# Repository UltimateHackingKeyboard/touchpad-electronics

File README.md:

Ultimate Hacking Keyboard touchpad module
=========================================

Contained are the schematics and board layout KiCad files for the [Ultimate Hacking Keyboard](https://ultimatehackingkeyboard.com/) touchpad module.

Make sure to clone this repo with:

`git clone --recursive git@github.com:UltimateHackingKeyboard/touchpad-electronics.git`

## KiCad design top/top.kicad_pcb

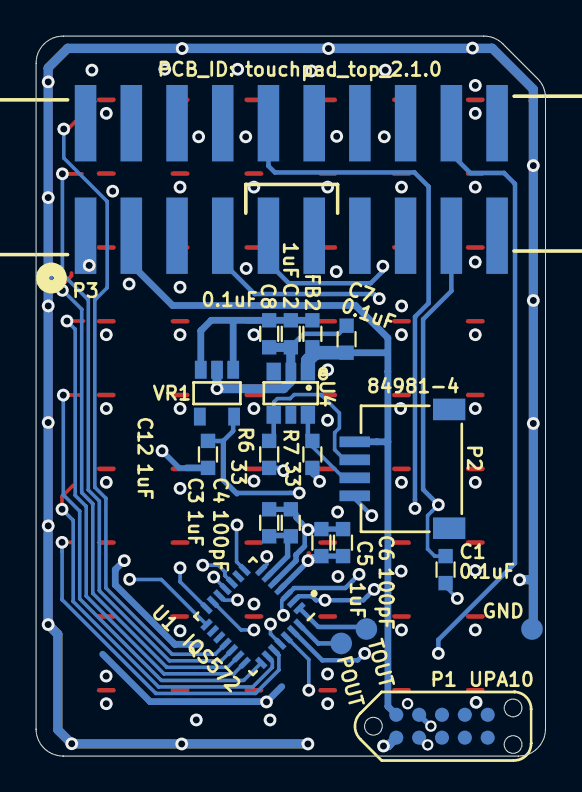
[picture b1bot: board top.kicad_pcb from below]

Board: 4 copper layers, 28.3 x 40.0 mm, 21 parts (21 on the bottom side), 14 nets.

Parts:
C1, C7, C8: 0.1uF; SM0603
C2, C3, C5, C12: 1uF; SM0603
C4, C6: 100pF; SM0603
FB2: FERRITE_BEAD; SM0603
P1: CONN_10; Tag_Connect_2x5_Header_With_No_Legs_Parallel_Numbering
P2: CONN_5; 84981-4
P3: CONN_20; MC-254-20-00-ST-SMD
R6, R7: 33; SM0603
TP_GND1: GND; Test_Point
TP_POUT1: POUT; Test_Point
TP_TOUT1: TOUT; Test_Point
U1: IQS572; QFN-28_4.3x4.3_Pitch0.5mm
U4: ESD; SC-74-TVS
VR1: MIC5504-3.3YM5; SOT-23-5

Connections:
+3V3: C5.2, C6.2, C12.2, U1.4, VR1.5
+5V: C2.2, C8.2, FB2.2, VR1.1, VR1.3
/NRST: C1.2, P3.17, U1.7
/PGM: P3.18, U1.27
/RDY: P3.10, U1.8
/SCL: P1.3, P3.9, R6.1, U1.3
/SCL_BOTTOM: P2.3, R6.2, U4.4
/SDA: P1.4, P3.7, R7.1, U1.2
/SDA_BOTTOM: P2.2, R7.2, U4.5
/VCC_BOTTOM: C7.2, FB2.1, P1.2, P2.4, P3.3, U4.1
GND: C1.1, C2.1, C3.1, C4.1, C5.1, C6.1, C7.1, C8.1, C12.1, P1.1, P2.1, P3.1, TP_GND1.1, U1.5, U4.2, VR1.2
unnamed: C3.2, C4.2, U1.6
unnamed: TP_POUT1.1, U1.28
unnamed: TP_TOUT1.1, U1.1

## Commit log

2019-07-03 Add root project file.
2019-07-03 Add gitignore.
2019-07-03 Add UGL KiCad lib as a git submodule.
2019-07-06 Add top board.
2019-07-06 Add bottom touchpad board.
2019-07-06 Put keepout areas to their actual layer.
2019-07-06 Add pogo pin connector.
2019-07-06 Add FFC connector on the bottom board.
2019-07-06 Add bottom schematic and route bottom board.
2019-07-06 Improve silk screen.
2019-07-06 Add top FFC connector.
2019-07-07 Replace circles with holes.
2019-07-07 Update description.
2019-07-11 Update library references.
2019-07-11 Add missing keepout areas.
2019-07-11 Add keepout areas.
2019-07-12 Update library reference.
2019-07-12 Add schematic and library links.
2019-07-12 Touch pattern #1.
2019-07-12 Touch pattern #2.
2019-07-12 Increase track width on bottom PCB.
2019-07-12 Annotate schematic.
2019-07-12 Add via pattern.
2019-07-12 Change touchpad sensor footprint. GND ring added to PCB.
2019-07-12 Change SDA and SCL lines.
2019-07-12 Change I2C lines on top schematic and rename test points.
2019-07-12 End of day commit. (Unrouted pattern.)
2019-07-15 Add libs readme.
2019-07-16 First final version of PCB and SCH.
2019-07-16 Change tag connector 2x3 to 2x5.
2019-07-17 Change UPA header pinout.
2019-07-17 Use +5V instead of +3V3 on programmer connector.
2019-07-17 Connect unconnected wires and remove the diamond pattern from the bottom left corner.
2019-07-17 Change touch controller footprint.
2019-08-05 Ignore generated BOM.
2019-08-06 Feature connector part names on the bottom board.
2019-08-07 Clean up silk screen.
2019-08-07 Update bottom board according to new CAD files.
2019-08-07 Update top board according to CAD.
2019-08-07 Add UHK logos.
2019-08-09 Tweak silk screen a little bit.
2019-08-09 Add UPA14 text.
2019-08-10 Rename UPA14 to UPA10.
2019-08-11 Update wiring according to new contour.
2019-08-11 Set trace clearance to 0.16 mm to make DRC succeed. Refill zones.
2019-08-11 Fix hole sizes and their keepout aeras.
2019-08-15 Add hole clearances.
2019-08-15 Add power library.
2019-08-15 Add readme.
2019-08-16 Rename 2K2 to 2.2K and improve silk screen.
2019-08-16 Make logo virtual.
2019-08-16 Ignore *-bak
2019-08-16 Make logo virtual and make pogo pin through-hole.
2019-08-22 Maximize the distance between board edge and copper.
2019-08-22 Refill zones.
2019-10-04 Connect supply line to VCC_BOTTOM on programmer connector.
2019-10-04 Edit ESD GND ring.
2019-10-04 New diamond pattern.
2019-11-22 Wiring new pattern.
2019-11-25 First final modified board.
2019-11-27 Add a config header.
2019-12-04 Fix DRC errors.
2019-12-15 Improved GND layer. (Add zone array to swapped inner layer.)
2019-12-18 Add GND shield between RX and TX lines.
2019-12-18 Bump version number of the top board and schematic to 2.0.0
2020-01-01 Don't put paste on the pads of the large 2x10 header.
2020-01-24 Make the 20 pin header virtual.
2020-03-05 Add license.
2020-04-05 Use consistent label font size.
2020-05-18 Remove redundant I2C pull-up resistors.
2020-05-18 Move bypass caps closer to pin 4.
2020-05-18 Reposition the FFC connector.
2020-05-18 Replace 47 ohm resistors with 33 ohm ones.
2020-05-18 Bump top board version to 2.1.0
2020-05-19 Update board based on CAD.
2020-06-02 Fix touchpad keepout area.
2020-06-10 Capitalize UGL library name for the schematic.
2020-06-10 Capitalize UGL library name for the board.
2020-06-11 Tweak plot parameters.
2020-06-11 Arrange components on the schematic more evenly.
2020-06-11 Rename top* to touchpad-top*
2020-06-11 Rename bottom* to touchpad-bottom*
2020-08-03 Update HLW4R-2C7LF featuring enlarged annular rings and reposition the UHK logo and PCB ID text.
2020-08-03 Bump the version of the bottom board to 2.2.0
2020-08-17 Remove P3 connector and TOUT and POUT testpoints.
2020-08-17 Improved routing and modified desig rules.
2020-08-17 Increased GND ring near board edge.
2020-08-17 Swap RDY and NRST paths.
2020-08-18 Improved VIA positions.
2020-08-18 Wiring.
2020-08-18 Bump the board versions to 2.2.0
2020-08-19 Improve wiring to optimize manufacturing.
2020-08-30 Remove NRST and PGM signals from TAG connector.
2020-08-30 Clean up silk screen text.
2020-08-30 Add UHK logo.
2020-08-30 Adjust silk screen.
2020-09-04 Library update.
2020-09-04 Add GND island into capacitive pads.
2020-09-05 Bump top board version to 2.3.0
2020-09-28 Modified SCL and SDA routing.
2020-09-28 Change board stackup and remove gnd islands.
2020-09-28 Arrange components outside of pcb.
2020-09-28 Add RX and TX paths.
2020-09-28 Temporarí commit.
2020-09-28 End of day commit.
2020-09-29 Temporary commit
2020-09-29 Add GND zone.
2020-09-29 Final routing.
2020-09-29 Finish silkscreen and increase version number.
2020-10-02 Bump version to 3.0.0 and tidy up silk screen a bit.
2020-10-08 New sensor grid. (0.15mm sensor gap)
2020-10-08 Reconnect all sensors.
2020-10-08 Add GND island to sensors.
2020-10-08 Change design rules.
2020-10-08 Change version number to 3.1.0.
2020-10-13 Improve silk screen for AOI.
2020-10-13 Bump top board version to 4.0.0
2020-11-10 Decrease width of ESD ring and add half gnd pads to diamonds.
2020-11-10 Change gnd pads to increased sized.
2020-11-10 Add arcs to ESD ring.
2020-11-10 Add dummy arcs to F.Cu (smoother zone corners).
2020-11-10 Add smd pads to diamonds and update library reference.
2020-11-10 Add 0R resistor to RDY signal.
2020-11-10 Temp. commit.
2020-11-10 Routing.
2020-11-10 Final version.
2020-11-11 Make R1 0 ohm instead of 33 ohm.
2020-11-11 Spruce up silk screen.
2020-11-11 Bump board version to 5.0.0
2020-12-13 Make F.Cu layer visible.
2020-12-14 Make QFN-28_4.3x4.3_Pitch0.5mm orientation marker easier to see.
2020-12-14 Bump version to 5.0.1
2020-12-14 Make the F.Cu layer visible again.
2020-12-17 Modified contour.
2021-02-04 Set the FFC connector of the top touchpad board to SMD instead of through-hole.
2021-11-15 Update submodule URL.
